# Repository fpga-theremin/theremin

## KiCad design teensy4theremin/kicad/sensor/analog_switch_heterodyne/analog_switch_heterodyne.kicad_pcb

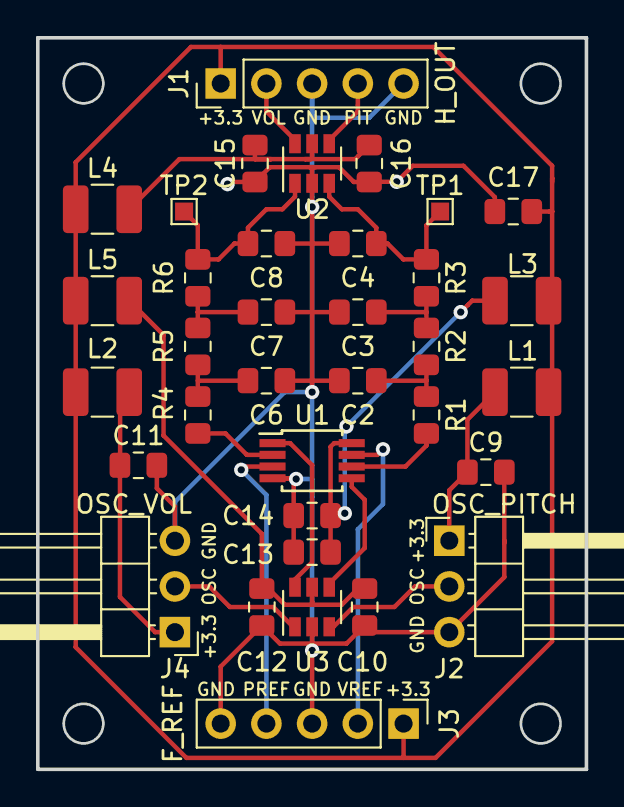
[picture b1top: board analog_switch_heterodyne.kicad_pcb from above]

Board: 2 copper layers, 30.5 x 40.6 mm, 35 parts (0 on the bottom side), 23 nets.

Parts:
C2, C3, C4, C6, C7, C8: 100pF; C_0805_2012Metric_Pad1.15x1.40mm_HandSolder
C9, C11, C12, C13, C15: 1uF; C_0805_2012Metric_Pad1.15x1.40mm_HandSolder
C10, C14, C16: 0.1uF; C_0805_2012Metric_Pad1.15x1.40mm_HandSolder
C17: 2.2uF; C_0805_2012Metric_Pad1.15x1.40mm_HandSolder
J1: H_OUT; PinHeader_1x05_P2.54mm_Vertical
J2: OSC_PITCH; PinHeader_1x03_P2.54mm_Horizontal
J3: F_REF; PinHeader_1x05_P2.54mm_Vertical
J4: OSC_VOL; PinHeader_1x03_P2.54mm_Horizontal
L1, L2, L3, L4, L5: Ferrite 10uH; L_1210_3225Metric_Pad1.42x2.65mm_HandSolder
R1, R4: 100; R_0805_2012Metric_Pad1.15x1.40mm_HandSolder
R2, R5: 4.7K; R_0805_2012Metric_Pad1.15x1.40mm_HandSolder
R3, R6: 47K; R_0805_2012Metric_Pad1.15x1.40mm_HandSolder
TP1: PITCH_FLT; TestPoint_Pad_1.0x1.0mm
TP2: VOL_FLT; TestPoint_Pad_1.0x1.0mm
U1: ADG721BRMZ; MSOP-8_3x3mm_P0.65mm
U2, U3: 2G04; SOT-23-6

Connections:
+3V3: C17.1, J1.1, J3.1, L1.1, L2.1, L3.1, L4.1, L5.1
/3.3V_1: C9.1, J2.1, L1.2
/3.3V_2: C11.1, J4.1, L2.2
/FREF_PITCH: J3.4, U1.3
/FREF_VOL: J3.2, U1.7
/HOUT_PITCH: J1.4, U2.4
/HOUT_VOL: J1.2, U2.6
/OSC_PITCH: J2.2, U3.3
/OSC_VOL: J4.2, U3.1
/VCC_U1: C13.1, C14.1, L3.2, U1.8
/VCC_U2: C15.1, C16.1, L4.2, U2.5
/VCC_U3: C10.1, C12.1, L5.2, U3.5
GND: C2.2, C3.2, C4.2, C6.2, C7.2, C8.2, C9.2, C10.2, C11.2, C12.2, C13.2, C14.2, C15.2, C16.2, C17.2, J1.3, J1.5, J2.3, J3.3, J3.5, J4.3, U1.4, U2.2, U3.2
unnamed: C2.1, R1.1, R2.2
unnamed: C3.1, R2.1, R3.2
unnamed: C4.1, R3.1, TP1.1, U2.3
unnamed: C6.1, R4.1, R5.2
unnamed: C7.1, R5.1, R6.2
unnamed: C8.1, R6.1, TP2.1, U2.1
unnamed: R1.2, U1.6
unnamed: R4.2, U1.2
unnamed: U1.1, U3.6
unnamed: U1.5, U3.4

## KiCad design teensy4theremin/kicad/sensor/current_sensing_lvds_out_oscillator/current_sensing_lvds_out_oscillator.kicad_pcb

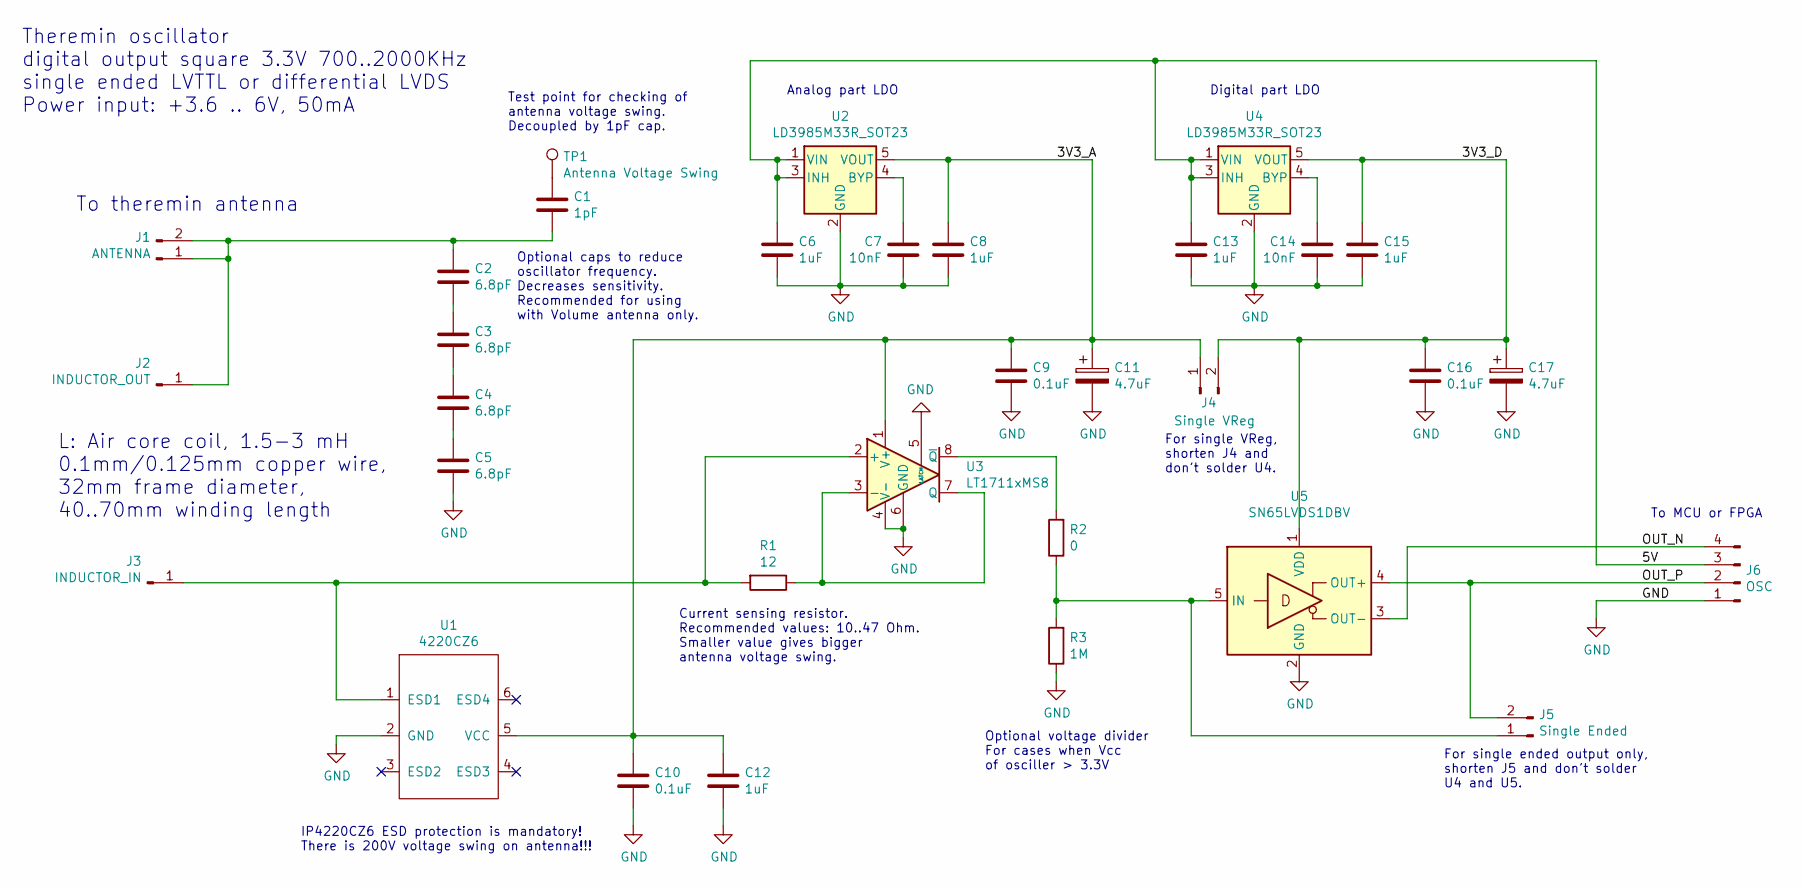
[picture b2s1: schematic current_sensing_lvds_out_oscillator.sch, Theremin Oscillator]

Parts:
C1: 1pF; C_0805_2012Metric_Pad1.15x1.40mm_HandSolder
C2, C3, C4, C5: 6.8pF; C_0805_2012Metric_Pad1.15x1.40mm_HandSolder
C6, C8, C12, C13, C15: 1uF; C_0805_2012Metric_Pad1.15x1.40mm_HandSolder
C7, C14: 10nF; C_0805_2012Metric_Pad1.15x1.40mm_HandSolder
C9, C10, C16: 0.1uF; C_0805_2012Metric_Pad1.15x1.40mm_HandSolder
C11, C17: 4.7uF; CP_EIA-3528-21_Kemet-B_Pad1.50x2.35mm_HandSolder
J1: ANTENNA; PinHeader_1x02_P2.54mm_Horizontal
J2: INDUCTOR_OUT; PinHeader_1x01_P2.54mm_Horizontal
J3: INDUCTOR_IN; PinHeader_1x01_P2.54mm_Horizontal
J4: Single VReg; PinHeader_1x02_P1.27mm_Vertical
J5: Single Ended; PinHeader_1x02_P1.27mm_Vertical
J6: OSC; PinHeader_1x04_P2.54mm_Horizontal
R1: 12; R_0805_2012Metric_Pad1.20x1.40mm_HandSolder
R2: 0; R_0805_2012Metric_Pad1.20x1.40mm_HandSolder
R3: 1M; R_0805_2012Metric_Pad1.20x1.40mm_HandSolder
TP1: Antenna Voltage Swing; PinHeader_1x01_P1.27mm_Vertical
U1: 4220CZ6; TSOP-6_1.65x3.05mm_P0.95mm
U2, U4: LD3985M33R_SOT23; SOT-23-5
U3: LT1711xMS8; MSOP-8_3x3mm_P0.65mm
U5: SN65LVDS1DBV; SOT-23-5

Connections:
/3V3_A: C8.1, C9.1, C10.1, C11.1, C12.1, J4.1, U1.5 (VCC), U2.5 (VOUT), U3.1 (V+)
/3V3_D: C15.1, C16.1, C17.1, J4.2, U4.5 (VOUT), U5.1 (VDD)
/5V: C6.1, C13.1, J6.3, U2.1 (VIN), U2.3 (INH), U4.1 (VIN), U4.3 (INH)
/OUT_N: J6.4, U5.3 (OUT-)
/OUT_P: J5.2, J6.2, U5.4 (OUT+)
GND: C5.2, C6.2, C7.2, C8.2, C9.2, C10.2, C11.2, C12.2, C13.2, C14.2, C15.2, C16.2, C17.2, J6.1, R3.1, U1.2 (GND), U2.2 (GND), U3.4 (V-), U3.5 (LATCH), U3.6 (GND), U4.2 (GND), U5.2 (GND)
unnamed: C1.1, TP1.1
unnamed: C1.2, C2.1, J1.1, J1.2, J2.1
unnamed: C2.2, C3.1
unnamed: C3.2, C4.1
unnamed: C4.2, C5.1
unnamed: C7.1, U2.4 (BYP)
unnamed: C14.1, U4.4 (BYP)
unnamed: J3.1, R1.2, U1.1 (ESD1), U3.2 (+)
unnamed: J5.1, R2.1, R3.2, U5.5 (IN)
unnamed: R1.1, U3.3 (-), U3.7 (Q)
unnamed: R2.2, U3.8 (~Q)

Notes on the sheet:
To theremin antenna
Theremin oscillator digital output square 3.3V 700..2000KHz single ended LVTTL or differential LVDS Power input: +3.6 .. 6V, 50mA
L: Air core coil, 1.5-3 mH 0.1mm/0.125mm copper wire, 32mm frame diameter, 40..70mm winding length
IP4220CZ6 ESD protection is mandatory! There is 200V voltage swing on antenna!!!
Analog part LDO
Digital part LDO
To MCU or FPGA
Optional caps to reduce oscillator frequency. Decreases sensitivity. Recommended for using with Volume antenna only.
Test point for checking of antenna voltage swing. Decoupled by 1pF cap.
Current sensing resistor. Recommended values: 10..47 Ohm. Smaller value gives bigger antenna voltage swing.
For single ended output only, shorten J5 and don't solder U4 and U5.
For single VReg, shorten J4 and don't solder U4.
Optional voltage divider For cases when Vcc of osciller > 3.3V

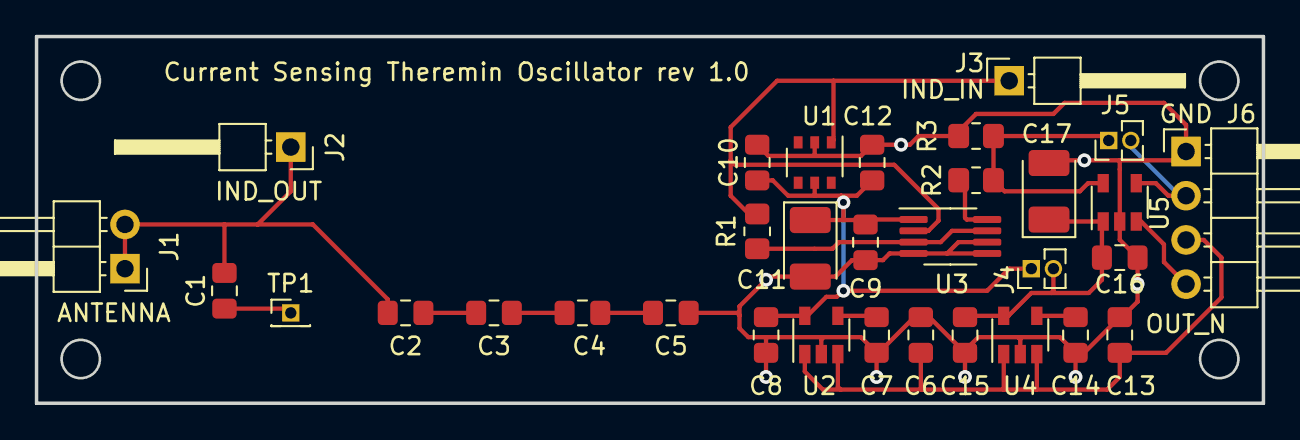
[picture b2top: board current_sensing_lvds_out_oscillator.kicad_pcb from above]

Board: 2 copper layers, 70.5 x 21.1 mm, 32 parts (0 on the bottom side), 17 nets.

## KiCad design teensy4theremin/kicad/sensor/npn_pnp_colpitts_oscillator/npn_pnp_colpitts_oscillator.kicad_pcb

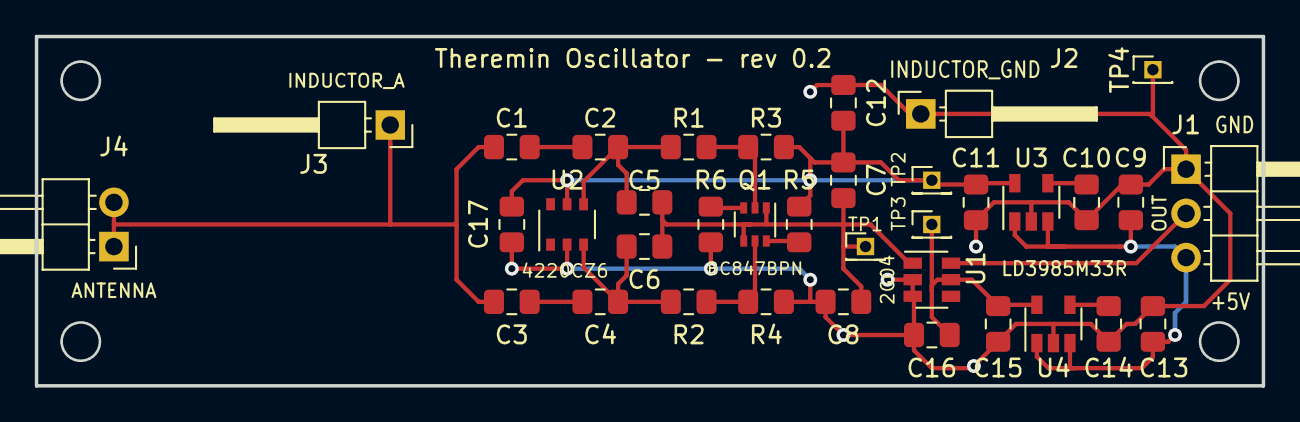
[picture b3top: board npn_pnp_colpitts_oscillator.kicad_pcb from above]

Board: 2 copper layers, 70.5 x 20.1 mm, 36 parts (0 on the bottom side), 17 nets.

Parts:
C1, C2, C3, C4: 6.8pF; C_0805_2012Metric_Pad1.15x1.40mm_HandSolder
C5, C6, C7, C8: 330pF; C_0805_2012Metric_Pad1.15x1.40mm_HandSolder
C9, C11, C13, C15: 1uF; C_0805_2012Metric_Pad1.15x1.40mm_HandSolder
C10, C14: 10nF; C_0805_2012Metric_Pad1.15x1.40mm_HandSolder
C12, C16: 0.1uF; C_0805_2012Metric_Pad1.15x1.40mm_HandSolder
C17: 0.22uF; C_0805_2012Metric_Pad1.15x1.40mm_HandSolder
J1: OSC; PinHeader_1x03_P2.54mm_Horizontal
J2: INDUCTOR_G; PinHeader_1x01_P2.54mm_Horizontal
J3: INDUCTOR_A; PinHeader_1x01_P2.54mm_Horizontal
J4: ANTENNA; PinHeader_1x02_P2.54mm_Horizontal
Q1: BC847BPN; SOT-363_SC-70-6
R1, R2: 1K; R_0805_2012Metric_Pad1.15x1.40mm_HandSolder
R3, R4: 120K; R_0805_2012Metric_Pad1.15x1.40mm_HandSolder
R5, R6: 47; R_0805_2012Metric_Pad1.15x1.40mm_HandSolder
TP1: OSC; PinHeader_1x01_P1.27mm_Vertical
TP2: 3V3_Analog; PinHeader_1x01_P1.27mm_Vertical
TP3: TestPoint; PinHeader_1x01_P1.27mm_Vertical
TP4: GND; PinHeader_1x01_P1.27mm_Vertical
U1: 2G04; SOT-23-6
U2: 4220CZ6; TSOP-6_1.65x3.05mm_P0.95mm
U3, U4: LD3985M33R_SOT23; SOT-23-5

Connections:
/3V3_A: C7.1, C11.1, C12.1, C17.1, R3.2, R5.2, TP2.1, U2.5, U3.5
/3V3_D: C15.1, C16.1, TP3.1, U1.5, U4.5
/5V: C9.1, C13.1, J1.3, U3.1, U3.3, U4.1, U4.3
/OSC_OUT: J1.2, U1.6
GND: C8.2, C9.2, C10.2, C11.2, C12.2, C13.2, C14.2, C15.2, C16.2, C17.2, J1.1, J2.1, R4.1, R6.1, TP4.1, U1.2, U1.3, U2.2, U3.2, U4.2
unnamed: C1.1, C3.1, J3.1, J4.1, J4.2
unnamed: C1.2, C2.1
unnamed: C2.2, C5.2, R1.1, U2.4
unnamed: C3.2, C4.1
unnamed: C4.2, C6.1, R2.1, U2.3
unnamed: C5.1, C6.2, C7.2, C8.1, Q1.1, Q1.4, TP1.1, U1.1
unnamed: C10.1, U3.4
unnamed: C14.1, U4.4
unnamed: Q1.2, R1.2, R3.1
unnamed: Q1.3, R6.2
unnamed: Q1.5, R2.2, R4.2
unnamed: Q1.6, R5.1

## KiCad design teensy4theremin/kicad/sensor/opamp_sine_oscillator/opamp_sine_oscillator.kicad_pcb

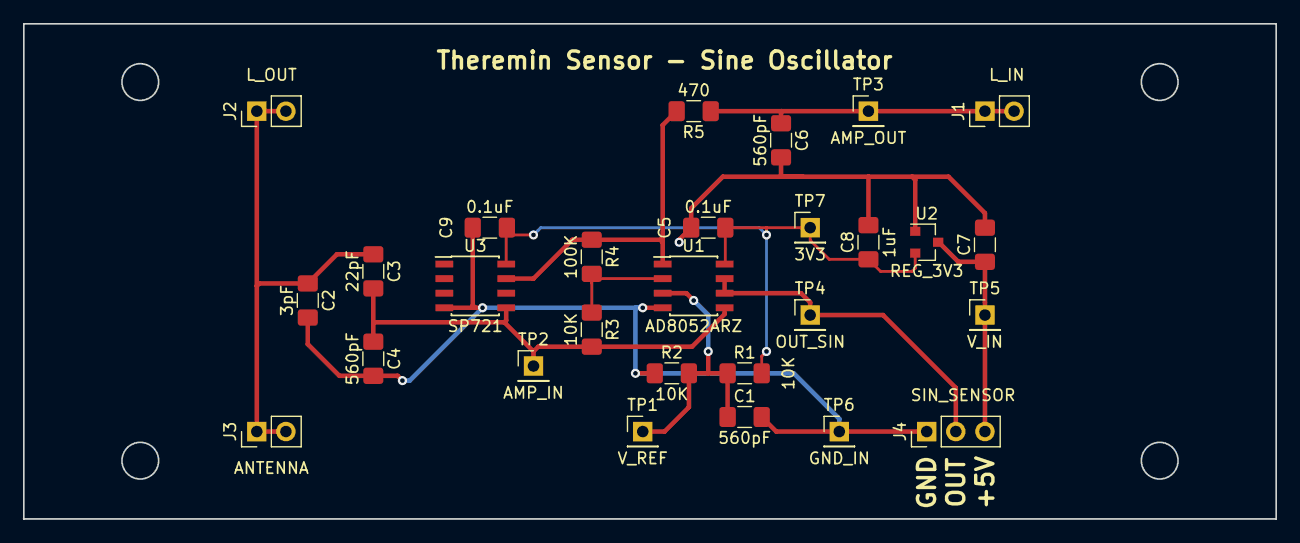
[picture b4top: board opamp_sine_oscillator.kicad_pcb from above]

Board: 2 copper layers, 109.2 x 43.2 mm, 28 parts (0 on the bottom side), 10 nets.

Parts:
C1, C4, C6: 560pF; C_1206_3216Metric_Pad1.42x1.75mm_HandSolder
C2: 3pF; C_1206_3216Metric_Pad1.42x1.75mm_HandSolder
C3: 22pF; C_1206_3216Metric_Pad1.42x1.75mm_HandSolder
C5, C9: 0.1uF; C_1206_3216Metric_Pad1.42x1.75mm_HandSolder
C7, C8: 1uF; C_1206_3216Metric_Pad1.42x1.75mm_HandSolder
J1: L_IN; PinHeader_1x02_P2.54mm_Vertical
J2: L_OUT; PinHeader_1x02_P2.54mm_Vertical
J3: ANTENNA; PinHeader_1x02_P2.54mm_Vertical
J4: SIN_SENSOR; PinHeader_1x03_P2.54mm_Vertical
R1, R2, R3: 10K; R_1206_3216Metric_Pad1.42x1.75mm_HandSolder
R4: 100K; R_1206_3216Metric_Pad1.42x1.75mm_HandSolder
R5: 470; R_1206_3216Metric_Pad1.42x1.75mm_HandSolder
TP1: V_REF; PinHeader_1x01_P2.54mm_Vertical
TP2: AMP_IN; PinHeader_1x01_P2.54mm_Vertical
TP3: AMP_OUT; PinHeader_1x01_P2.54mm_Vertical
TP4: OUT_SIN; PinHeader_1x01_P2.54mm_Vertical
TP5: V_IN; PinHeader_1x01_P2.54mm_Vertical
TP6: GND_IN; PinHeader_1x01_P2.54mm_Vertical
TP7: 3V3; PinHeader_1x01_P2.54mm_Vertical
U1: AD8052ARZ; SOIC-8_3.9x4.9mm_P1.27mm
U2: REG_3V3; SOT-23
U3: SP721; SOIC-8_3.9x4.9mm_P1.27mm

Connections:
+3V3: C5.1, C8.1, C9.1, R1.2, TP7.1, U1.8, U2.2, U3.8
+5V: C7.1, J4.3, TP5.1, U2.3
/ESD1: C3.2, C4.1, R3.2, TP2.1, U1.5, U3.5
/ESD2: R4.1, R5.2, U1.1, U3.7
/VREF: C1.1, R1.1, R2.2, TP1.1, U1.3
GND: C1.2, C2.2, C4.2, C5.2, C6.2, C7.2, C8.2, C9.2, J4.1, R2.1, TP6.1, U1.4, U2.1, U3.4
unnamed: C2.1, C3.1, J2.1, J2.2, J3.1, J3.2
unnamed: C6.1, J1.1, J1.2, R5.1, TP3.1
unnamed: J4.2, TP4.1, U1.6, U1.7
unnamed: R3.1, R4.2, U1.2

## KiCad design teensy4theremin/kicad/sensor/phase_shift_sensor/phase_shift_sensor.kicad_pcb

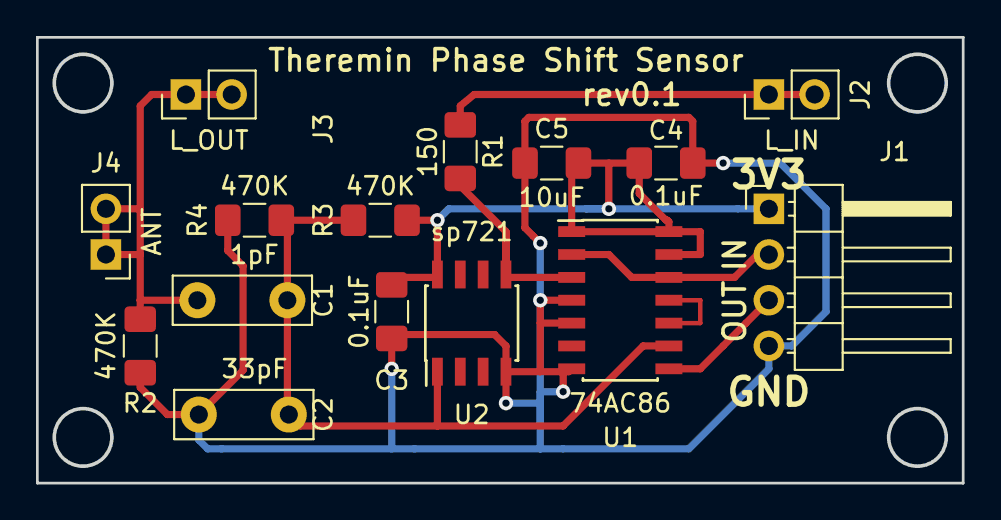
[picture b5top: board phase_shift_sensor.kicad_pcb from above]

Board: 2 copper layers, 51.4 x 24.8 mm, 15 parts (0 on the bottom side), 9 nets.

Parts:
C1: 1pF; C_Disc_D7.5mm_W2.5mm_P5.00mm
C2: 33pF; C_Disc_D7.5mm_W2.5mm_P5.00mm
C3, C4: 0.1uF; C_1206_3216Metric_Pad1.42x1.75mm_HandSolder
C5: 10uF; C_1206_3216Metric_Pad1.42x1.75mm_HandSolder
J1: SENSOR; PinHeader_1x04_P2.54mm_Horizontal
J2: L_IN; PinHeader_1x02_P2.54mm_Vertical
J3: L_OUT; PinHeader_1x02_P2.54mm_Vertical
J4: ANT; PinHeader_1x02_P2.54mm_Vertical
R1: 150; R_1206_3216Metric_Pad1.42x1.75mm_HandSolder
R2, R3, R4: 470K; R_1206_3216Metric_Pad1.42x1.75mm_HandSolder
U1: 74AC86; SOIC-14_3.9x8.7mm_P1.27mm
U2: sp721; SOIC-8_3.9x4.9mm_P1.27mm

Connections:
+3V3: C3.1, C4.1, C5.1, J1.1, R3.2, U1.1, U1.13, U1.14, U2.8
/PWM_OUT: J1.3, U1.8
/REF_CLK: J1.2, U1.2, U1.12
GND: C2.2, C3.2, C4.2, C5.2, J1.4, R2.1, R4.1, U1.4, U1.5, U1.7, U2.4
unnamed: C1.1, J3.1, J3.2, J4.1, J4.2, R2.2
unnamed: C1.2, C2.1, R3.1, R4.2, U1.9, U2.1
unnamed: J2.1, J2.2, R1.1
unnamed: R1.2, U1.3, U2.5
unnamed: U1.10, U1.11

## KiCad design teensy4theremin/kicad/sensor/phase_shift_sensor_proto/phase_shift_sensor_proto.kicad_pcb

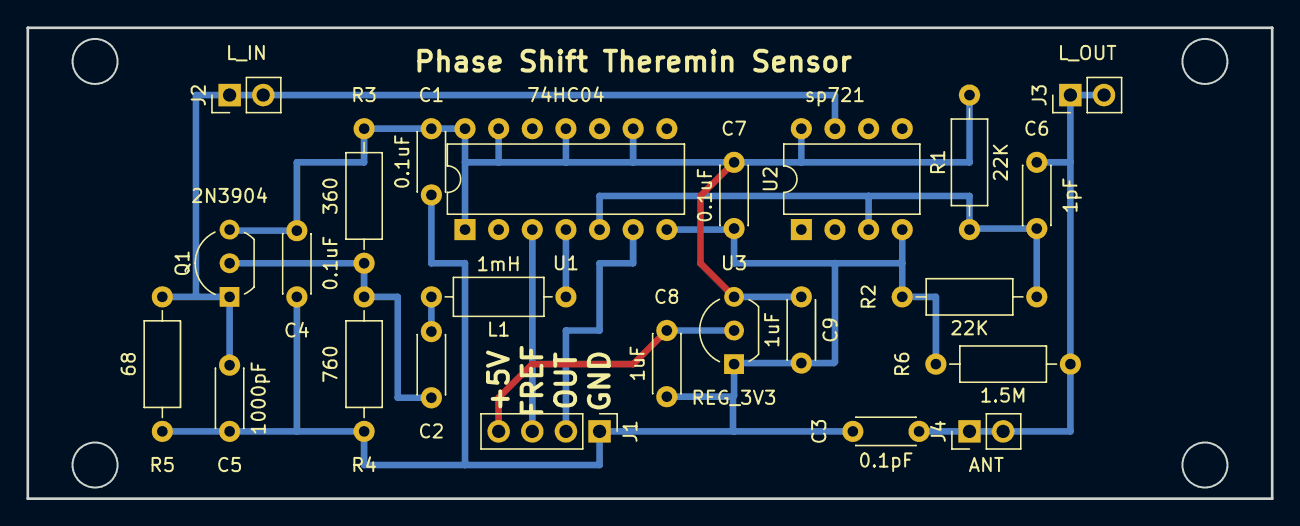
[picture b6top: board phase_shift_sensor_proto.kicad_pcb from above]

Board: 2 copper layers, 94.0 x 35.6 mm, 24 parts (0 on the bottom side), 11 nets.

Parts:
C1, C4, C7: 0.1uF; C_Disc_D4.3mm_W1.9mm_P5.00mm
C2: 47pF; C_Disc_D4.3mm_W1.9mm_P5.00mm
C3: 0.1pF; C_Disc_D4.3mm_W1.9mm_P5.00mm
C5: 1000pF; C_Disc_D4.3mm_W1.9mm_P5.00mm
C6: 1pF; C_Disc_D4.3mm_W1.9mm_P5.00mm
C8, C9: 1uF; C_Disc_D4.3mm_W1.9mm_P5.00mm
J1: SENSOR; PinHeader_1x04_P2.54mm_Vertical
J2: L_IN; PinHeader_1x02_P2.54mm_Vertical
J3: L_OUT; PinHeader_1x02_P2.54mm_Vertical
J4: ANT; PinHeader_1x02_P2.54mm_Vertical
L1: 1mH; L_Axial_L6.6mm_D2.7mm_P10.16mm_Horizontal_Vishay_IM-2
Q1: 2N3904; TO-92_Inline_Wide
R1, R2: 22K; R_Axial_DIN0207_L6.3mm_D2.5mm_P10.16mm_Horizontal
R3: 360; R_Axial_DIN0207_L6.3mm_D2.5mm_P10.16mm_Horizontal
R4: 760; R_Axial_DIN0207_L6.3mm_D2.5mm_P10.16mm_Horizontal
R5: 68; R_Axial_DIN0207_L6.3mm_D2.5mm_P10.16mm_Horizontal
R6: 1.5M; R_Axial_DIN0207_L6.3mm_D2.5mm_P10.16mm_Horizontal
U1: 74HC04; DIP-14_W7.62mm
U2: sp721; DIP-8_W7.62mm
U3: REG_3V3; TO-92_Inline_Wide

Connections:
+3V3: C1.1, C4.2, C7.1, C9.1, Q1.3, R1.2, R3.2, U1.1, U1.9, U1.11, U1.13, U1.14, U2.8, U3.3
+5V: C8.1, J1.4, U3.2
/PWM_OUT: J1.2, U1.6
/REF_CLK: J1.3, U1.3
GND: C1.2, C3.1, C4.1, C5.1, C7.2, C8.2, C9.2, J1.1, R2.1, R4.1, R5.1, R6.1, U1.7, U2.4, U3.1
unnamed: C2.1, Q1.2, R3.1, R4.2
unnamed: C2.2, L1.2
unnamed: C3.2, C6.1, J3.1, J3.2, J4.1, J4.2, R6.2
unnamed: C5.2, J2.1, J2.2, Q1.1, R5.2, U2.7
unnamed: C6.2, R1.1, R2.2, U1.5, U2.3
unnamed: L1.1, U1.4
